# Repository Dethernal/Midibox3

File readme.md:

# MidiBox3

My attempt to make new Waveblaster-compatible interface board.

## Features

* Work with all current loop MIDI source
* Additional Note On volume control with rotary encoder
* Can work without microcontroller as simple interface board but other features will gone.

## Plans

Measure power consumption. What maximum current on +5V line is? Do I really need output filter and what parameters it must have? So, I need to characterize all imortant parameters.

Next, there are more components on PCB that really needed for working. Also some components are more expensive than necessary. It will be reasonable to find cheaper ones.

Finally, STM32F103CBT6 is a beast and I love it. It have USB support and I planned use it in next revision of PCB. I don't know about ADC out via USB, but as power source and MIDI in port it will definitely work. Maybe it also may work as HardMPU, but this will require special DOS driver and I think it has lower priority.

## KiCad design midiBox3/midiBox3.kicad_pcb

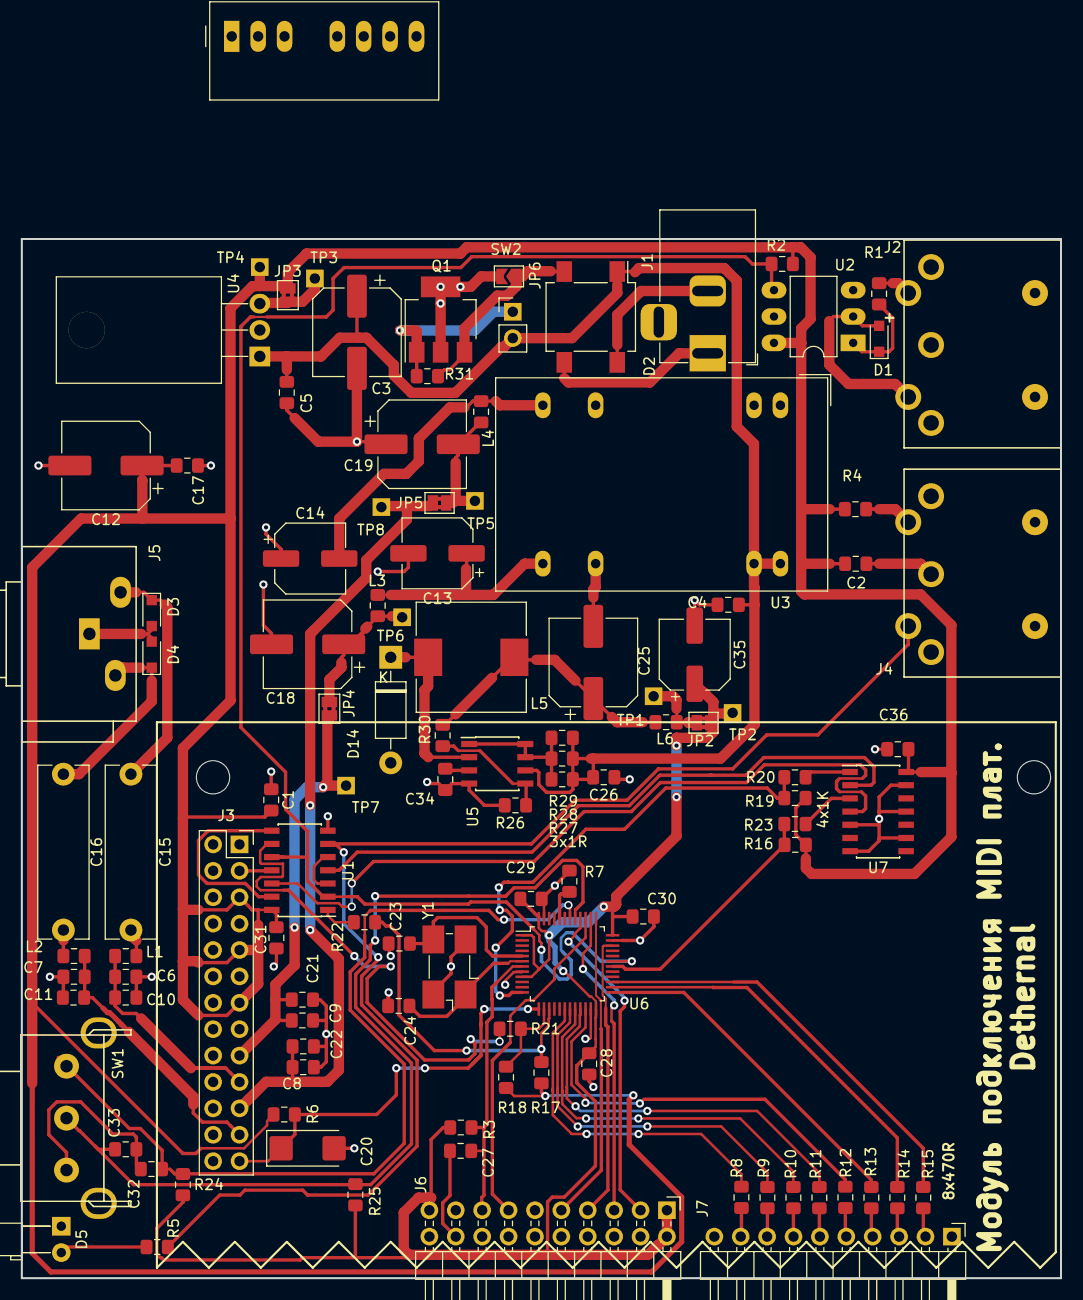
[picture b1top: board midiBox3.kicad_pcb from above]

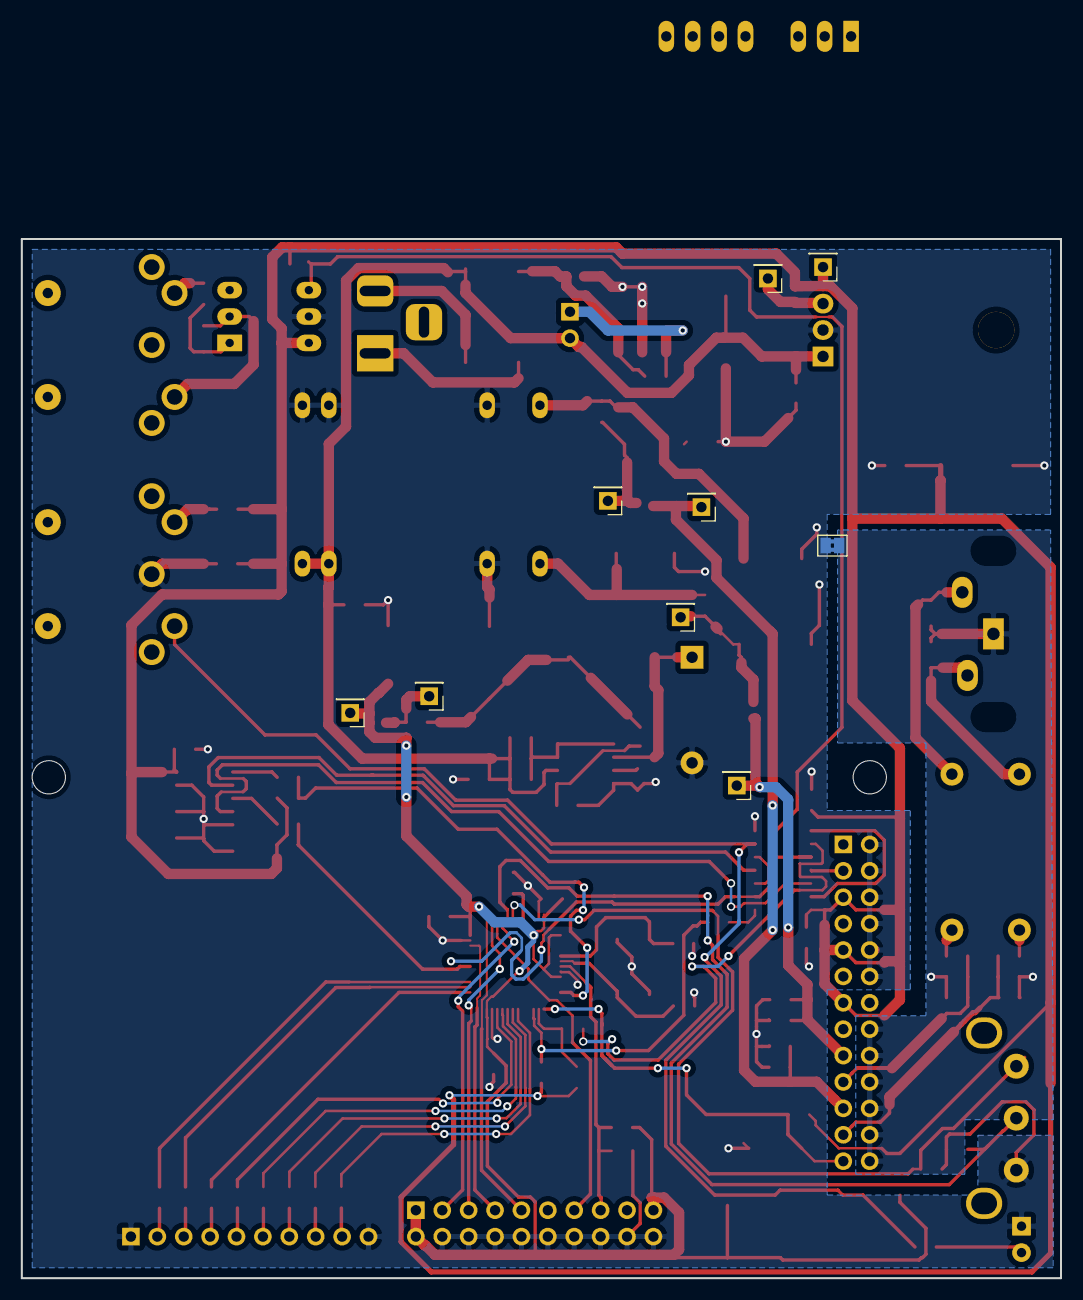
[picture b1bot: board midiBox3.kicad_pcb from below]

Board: 2 copper layers, 100.0 x 100.0 mm, 111 parts (9 on the bottom side), 76 nets.

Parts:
C1, C2, C8, C9, C27, C28, C31, C36: 100pF; C_0805_2012Metric_Pad1.15x1.40mm_HandSolder
C3, C12, C18, C19, C25: 220uF; CP_Elec_8x6.9
C4, C5, C17, C21, C22, C26: 1uF; C_0805_2012Metric_Pad1.15x1.40mm_HandSolder
C6, C7: 47pF; C_0805_2012Metric_Pad1.15x1.40mm_HandSolder
C10, C11, C23, C24: 15pF; C_0805_2012Metric_Pad1.15x1.40mm_HandSolder
C13, C14, C35: 47uF; CP_Elec_6.3x5.9
C15, C16: 1uF; C_Rect_L16.5mm_W4.7mm_P15.00mm_MKT
C20: 10uF; CP_EIA-6032-15_Kemet-U_Pad2.25x2.35mm_HandSolder
C29, C32, C33: 100nF; C_0805_2012Metric_Pad1.15x1.40mm_HandSolder
C30: 10nF; C_0805_2012Metric_Pad1.15x1.40mm_HandSolder
C34: 470pF; C_0805_2012Metric_Pad1.15x1.40mm_HandSolder
D1: 1N4148; D_SOD-323_HandSoldering
D2: DB104; Diode_Bridge_Vishay_DFSFlat
D3, D4: PESD5V0S1BA; D_SOD-323_HandSoldering
D5: LED; LED_D3.0mm_Horizontal_O3.81mm_Z2.0mm
D14: 1N5819; D_DO-41_SOD81_P10.16mm_Horizontal
J1: BarrelJack; BarrelJack_Horizontal
J2: DIN5 IN; DS-5-01
J3: WaveBlaster; PinSocket_2x13_P2.54mm_Vertical
J4: DIN5 OUT; DS-5-01
J5: RSA 2x; RCA_Dual_Jack_Board_RS-209_03x3mm_Vertical
J6: STM32_PROG; PinHeader_2x10_P2.54mm_Horizontal
J7: LED_CON; PinHeader_1x10_P2.54mm_Horizontal
JP1, JP2, JP3, JP4, JP5: SolderJumper-2_P1.3mm_Bridged2Bar_Pad1.0x1.5mm
JP6: shunt; SolderJumper-2_P1.3mm_Open_TrianglePad1.0x1.5mm
L1, L2: 100nH; L_0805_2012Metric_Pad1.15x1.40mm_HandSolder
L3, L4: 33nH; L_0805_2012Metric_Pad1.15x1.40mm_HandSolder
L5: 220 uH; L_10.4x10.4_H4.8
L6: 100 nH; L_0805_2012Metric_Pad1.15x1.40mm_HandSolder
Q1: IRFL110; SOT-223
R1: 510R; R_0805_2012Metric_Pad1.15x1.40mm_HandSolder
R2: 270R; R_0805_2012Metric_Pad1.15x1.40mm_HandSolder
R3, R6, R24, R25: 10K; R_0805_2012Metric_Pad1.15x1.40mm_HandSolder
R4: 220R; R_0805_2012Metric_Pad1.15x1.40mm_HandSolder
R5, R8, R9, R10, R11, R12, R13, R14, R15: 470R; R_0805_2012Metric_Pad1.15x1.40mm_HandSolder
R7: 4.7K; R_0805_2012Metric_Pad1.15x1.40mm_HandSolder
R16, R17, R18, R19, R20, R21, R22, R23: 1K; R_0805_2012Metric_Pad1.15x1.40mm_HandSolder
R26: 1.5K; R_0805_2012Metric_Pad1.15x1.40mm_HandSolder
R27, R28, R29: 1R; R_0805_2012Metric_Pad1.15x1.40mm_HandSolder
R30: 2.7K; R_0805_2012Metric_Pad1.15x1.40mm_HandSolder
R31: 22K; R_0805_2012Metric_Pad1.15x1.40mm_HandSolder
SW1: D_VALUE; Rotary_Encoder_Bourns_PEC16-2215F-N0024_Horizontal_16mm
SW2: SW_Reed; PinHeader_1x02_P2.54mm_Vertical
TP1, TP2, TP3, TP4, TP5, TP6, TP7, TP8: PinHeader_1x01_P2.54mm_Vertical
U1: 74HCT00; SOIC-14_3.9x8.7mm_P1.27mm
U2: H11L1; DIP-6_W7.62mm_LongPads
U3: JTE0624D12; Converter_DCDC_XP_POWER_JTExxxxDxx_THT
U4: L7805; TO-220-3_Horizontal_TabDown
U5: MC33063AD; SOIC-8_3.9x4.9mm_P1.27mm
U6: STM32F103CBT6; LQFP-48_7x7mm_P0.5mm
U7: 74ACT04; SOIC-14_3.9x8.7mm_P1.27mm
Y1: 16MHz; Crystal_SMD_0603-4Pin_6.0x3.5mm_HandSoldering

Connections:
+3V3: C28.2, C29.2, C30.2, C35.1, J6.1, J6.2, J6.19, JP2.2, R3.2, R24.2, R25.2, TP2.1, U6.1, U6.9, U6.24, U6.36, U6.48
+5V: C1.2, C2.2, C12.1, C17.1, C31.2, C36.2, J3.5, J3.9, J3.13, JP3.2, R2.2, R4.2, R6.1, R16.2, R17.2, R18.2, R19.2, TP4.1, U1.14, U2.6, U7.14
+12V: C9.1, C21.1, J3.17, JP4.2, TP7.1
-12V: C8.1, C22.2, J3.21, JP5.2, TP8.1
/+12NF: C13.1, L3.1, U3.14
/+IN12V: C3.1, C4.1, C5.1, C26.1, D2.1, R27.2, R28.2, R29.2, SW2.2, U3.22, U3.23, U4.1, U5.6
/-12NF: C14.2, L4.1, U3.11
/ENC_A: C33.2, R25.1, SW1.B, U6.41
/ENC_B: C32.1, R24.1, SW1.A, U6.42
/JNTRST: J6.3, U6.40
/JTCK_SWCLK: J6.9, U6.37
/JTDI: J6.5, U6.38
/JTDO-TRACESWO: J6.13, U6.39
/JTMS-SWDIO: J6.7, U6.34
/LEFT: C7.1, C11.1, J3.23, L2.1
/MIDI_IN: R2.1, U1.2, U1.10, U2.4, U6.31
/MIDI_N: D1.2, J2.4, U2.2
/MIDI_OUT_CON: R22.2, U1.1
/MIDI_P: D1.1, R1.1, U2.1
/MIDI_WB: J3.3, U1.11
/MIDI_WB_CON: R21.2, U1.9
/NRST: C27.2, J6.15, R3.1, U6.7
/RIGHT: C6.1, C10.1, J3.19, L1.1
/TX1: R23.2, U7.3
/TX2: R20.2, U7.1
/~RESET: C20.1, J3.25, R6.2, U6.13
GNDA: C6.2, C7.2, C10.2, C11.2, D3.2, D4.2, J3.16, J3.18, J3.20, J3.22, J3.24, J3.26, J5.3, JP1.2
GNDD: C1.1, C2.1, C3.2, C4.2, C5.2, C8.2, C9.2, C12.2, C13.2, C14.1, C17.2, C18.2, C19.1, C20.2, C21.2, C22.1, C23.2, C24.2, C25.2, C26.2, C27.1, C28.1, C29.1, C30.1, C31.1, C32.2, C33.1, C34.2, C35.2, C36.1, D5.1, D14.2, J3.2, J3.4, J3.6, J3.8, J3.10, J3.12, J4.2, J6.4, J6.6, J6.8, J6.10, J6.12, J6.14, J6.16, J6.18, J6.20, J7.1, J7.10, JP1.1, JP6.2, Q1.2, Q1.4, R7.2, R26.1, SW1.C, U1.7, U2.5, U3.2, U3.3, U3.9, U3.16, U4.2, U5.4, U6.8, U6.23, U6.35, U6.47, U7.5, U7.7, U7.9, U7.11, U7.13, Y1.2, Y1.4
unnamed: C15.1, D3.1, J5.1
unnamed: C15.2, L1.2
unnamed: C16.1, D4.1, J5.2
unnamed: C16.2, L2.2
unnamed: C18.1, JP4.1, L3.2, TP6.1
unnamed: C19.2, JP5.1, L4.2, TP5.1
unnamed: C23.1, U6.5, Y1.3
unnamed: C24.1, U6.6, Y1.1
unnamed: C25.1, L5.2, L6.1, R30.2
unnamed: C34.1, U5.3
unnamed: D2.2, JP6.1, Q1.3, R31.1
unnamed: D2.3, J1.1
unnamed: D2.4, J1.2
unnamed: D5.2, R5.1
unnamed: D14.1, L5.1, U5.2
unnamed: J2.5, R1.2
unnamed: J4.4, R5.2, U1.6
unnamed: J4.5, R4.1
unnamed: J7.2, R15.2
unnamed: J7.3, R14.2
unnamed: J7.4, R13.2
unnamed: J7.5, R12.2
unnamed: J7.6, R11.2
unnamed: J7.7, R10.2
unnamed: J7.8, R9.2
unnamed: J7.9, R8.2
unnamed: JP2.1, L6.2, TP1.1
unnamed: JP3.1, TP3.1, U4.3
unnamed: Q1.1, R31.2, SW2.1
unnamed: R7.1, U6.44
unnamed: R8.1, U6.18
unnamed: R9.1, U6.19
unnamed: R10.1, U6.20
unnamed: R11.1, U6.21
unnamed: R12.1, U6.22
unnamed: R13.1, U6.25
unnamed: R14.1, U6.26
unnamed: R15.1, U6.27
unnamed: R16.1, R23.1, U6.30
unnamed: R17.1, R22.1, U6.15
unnamed: R18.1, R21.1, U6.14
unnamed: R19.1, R20.1, U6.12
unnamed: R26.2, R30.1, U5.5
unnamed: R27.1, R28.1, R29.1, U5.1, U5.7, U5.8
unnamed: U1.3, U1.5
unnamed: U1.4, U7.2
unnamed: U1.12, U7.4
unnamed: U1.8, U1.13

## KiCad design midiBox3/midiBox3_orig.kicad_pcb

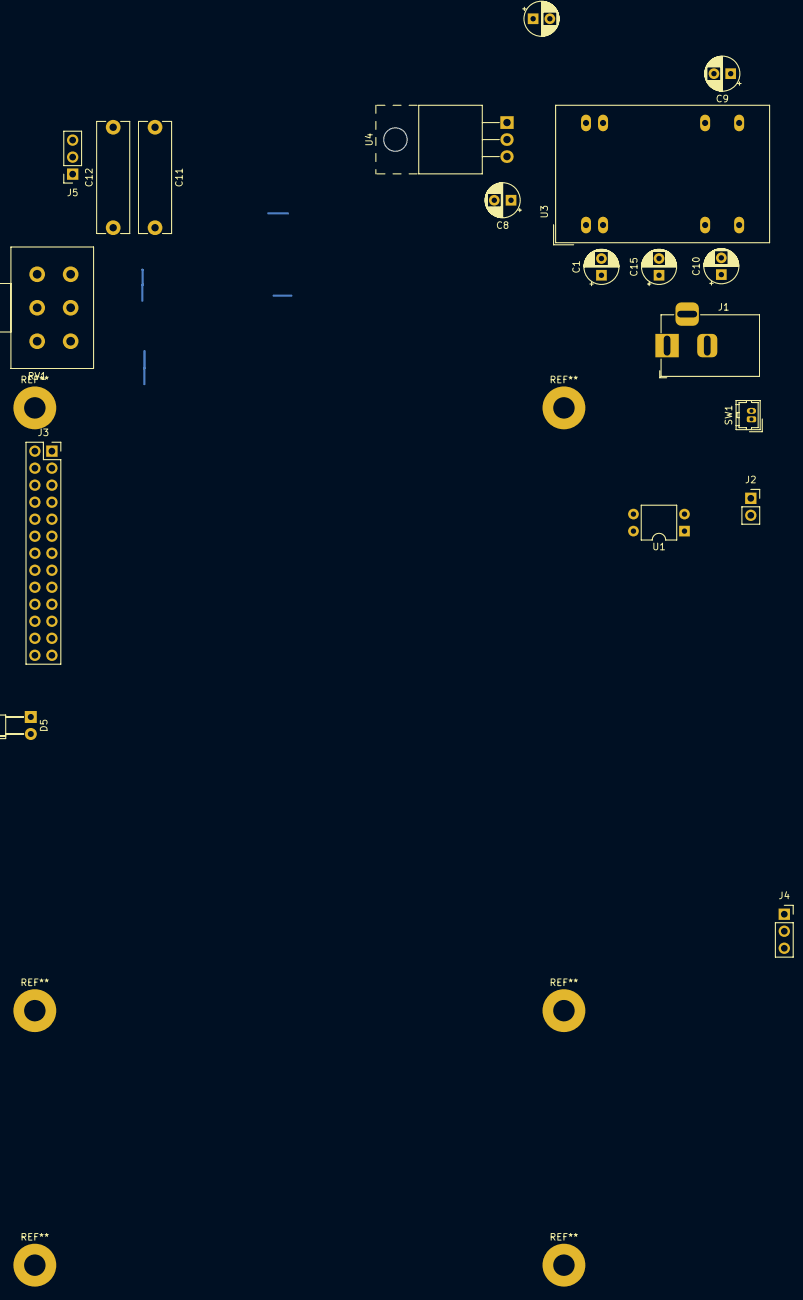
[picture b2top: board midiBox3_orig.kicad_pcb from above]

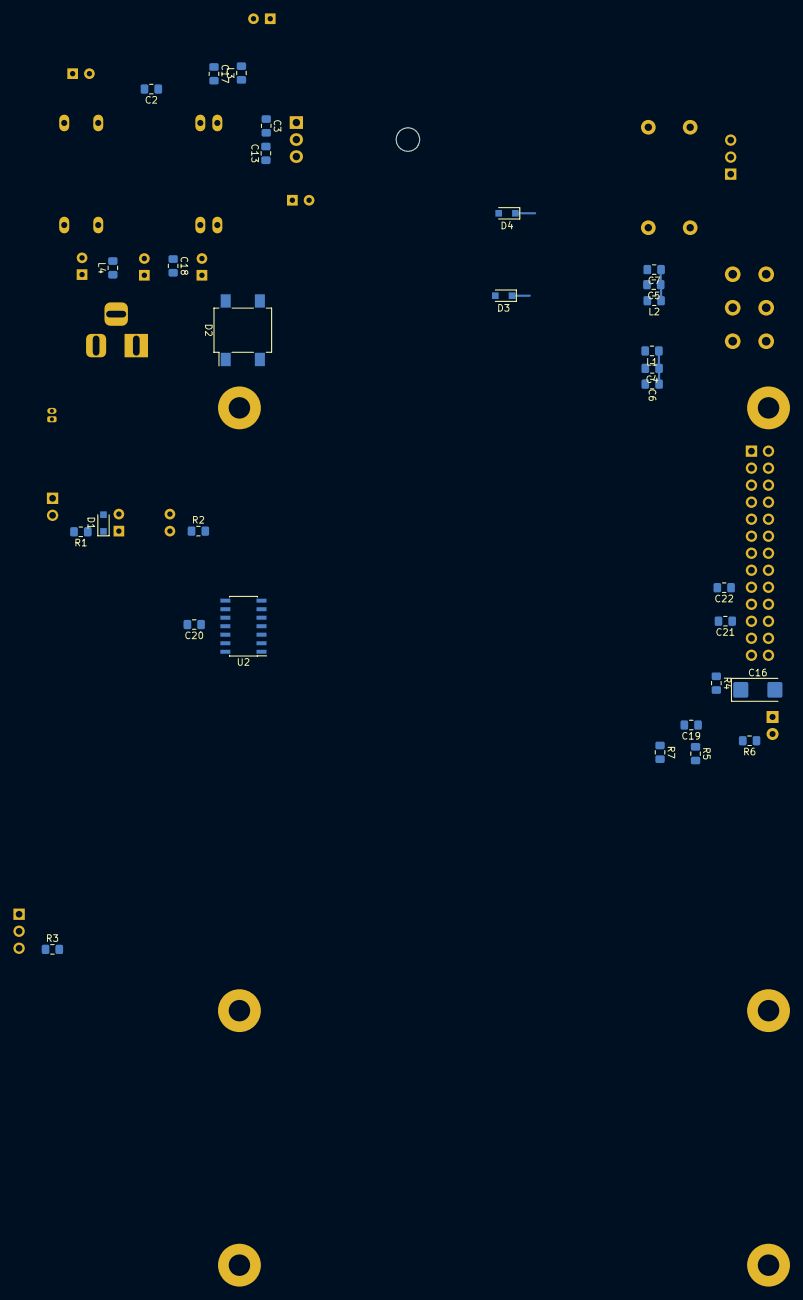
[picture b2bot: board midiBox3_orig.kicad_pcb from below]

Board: 2 copper layers, 49 parts (30 on the bottom side), 29 nets.

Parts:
C1, C8, C14, C15: 220uF; CP_Radial_D5.0mm_P2.50mm
C2, C3, C13, C17, C18: 1uF; C_0805_2012Metric_Pad1.15x1.40mm_HandSolder
C4, C5: 47pF; C_0805_2012Metric_Pad1.15x1.40mm_HandSolder
C6, C7: 15pF; C_0805_2012Metric_Pad1.15x1.40mm_HandSolder
C9, C10: 47uF; CP_Radial_D5.0mm_P2.50mm
C11, C12: 1uF; C_Rect_L16.5mm_W4.7mm_P15.00mm_MKT
C16: 10uF; CP_EIA-6032-15_Kemet-U_Pad2.25x2.35mm_HandSolder
C19, C20, C21, C22: 100pF; C_0805_2012Metric_Pad1.15x1.40mm_HandSolder
D1: 1N4148; D_SOD-323_HandSoldering
D2: DB104; Diode_Bridge_Vishay_DFSFlat
D3, D4: PESD5V0S1BA; D_SOD-323_HandSoldering
D5: LED; LED_D3.0mm_Horizontal_O3.81mm_Z2.0mm
J1: Barrel_Jack_Switch; BarrelJack_Horizontal
J2: H2; PinSocket_1x02_P2.54mm_Vertical
J3: Conn_02x13_Odd_Even; PinSocket_2x13_P2.54mm_Vertical
J4: H3; PinSocket_1x03_P2.54mm_Vertical
J5: Conn_Coaxial_x2; PinSocket_1x03_P2.54mm_Vertical
L1, L2: 100nH; L_0805_2012Metric_Pad1.15x1.40mm_HandSolder
L3, L4: 33nH; L_0805_2012Metric_Pad1.15x1.40mm_HandSolder
R1, R3: 220R; R_0805_2012Metric_Pad1.15x1.40mm_HandSolder
R2: 4.7K; R_0805_2012Metric_Pad1.15x1.40mm_HandSolder
R4: 10K; R_0805_2012Metric_Pad1.15x1.40mm_HandSolder
R5, R7: 0R; R_0805_2012Metric_Pad1.15x1.40mm_HandSolder
R6: 470R; R_0805_2012Metric_Pad1.15x1.40mm_HandSolder
RV1: R_POT_Dual; Potentiometer_Alps_RK163_Dual_Horizontal
SW1: SW_DIP_x01; Hirose_DF13-02P-1.25DSA_1x02_P1.25mm_Vertical
U1: PC817; DIP-4_W7.62mm
U2: MM74HCT00M; SOIC-14_3.9x8.7mm_P1.27mm
U3: JTE0624D12; Converter_DCDC_XP_POWER_JTExxxxDxx_THT
U4: LM7805_TO220; TO-220-3_Horizontal_TabUp

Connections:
+5V: C8.1, C13.1, C19.1, C20.1, J3.3, J3.5, J3.9, J3.13, R2.2, R3.2, R4.1, U2.11, U2.14, U4.3
+12V: C14.1, C17.1, C22.1, J3.17, L3.2
-12V: C15.1, C18.2, C21.1, J3.21, L4.2
/LEFT: J3.23, RV1.2
/RIGHT: J3.19, RV1.5
/~RESET: C16.1, J3.25, R4.2
GND: C1.2, C2.2, C3.2, C4.2, C5.2, C6.2, C7.2, C8.2, C9.2, C10.2, C13.2, C14.2, C15.2, C16.2, C17.2, C18.1, C19.2, C20.2, C21.2, C22.2, D2.4, D3.2, D4.2, D5.1, J3.2, J3.4, J3.6, J3.8, J3.10, J3.12, J3.16, J3.18, J3.20, J3.22, J3.24, J3.26, J4.2, J5.3, RV1.1, RV1.4, U1.3, U2.7, U3.2, U3.3, U3.9, U3.16, U4.2
unnamed: C1.1, C2.1, C3.1, D2.3, U3.22, U3.23, U4.1
unnamed: C4.1, C6.1, L1.1, RV1.6
unnamed: C5.1, C7.1, L2.1, RV1.3
unnamed: C9.1, L3.1, U3.14
unnamed: C10.1, L4.1, U3.11
unnamed: C11.1, D3.1, J5.1
unnamed: C11.2, L1.2
unnamed: C12.1, D4.1, J5.2
unnamed: C12.2, L2.2
unnamed: D1.1, R1.1, U1.1
unnamed: D1.2, J2.2, U1.2
unnamed: D2.1, SW1.2
unnamed: D2.2, J1.1
unnamed: D5.2, R6.1
unnamed: J1.2, SW1.1
unnamed: J2.1, R1.2
unnamed: J4.1, R7.2, U2.6
unnamed: J4.3, R3.1
unnamed: R2.1, U1.4, U2.1, U2.2, U2.9, U2.10
unnamed: R5.1, R6.2, R7.1
unnamed: R5.2, U2.3, U2.4, U2.5
unnamed: U2.8, U2.12, U2.13

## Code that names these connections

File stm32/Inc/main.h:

/* USER CODE BEGIN Header */
/**
  ******************************************************************************
  * @file           : main.h
  * @brief          : Header for main.c file.
  *                   This file contains the common defines of the application.
  ******************************************************************************
  * @attention
  *
  * <h2><center>&copy; Copyright (c) 2019 STMicroelectronics.
  * All rights reserved.</center></h2>
  *
  * This software component is licensed by ST under BSD 3-Clause license,
  * the "License"; You may not use this file except in compliance with the
  * License. You may obtain a copy of the License at:
  *                        opensource.org/licenses/BSD-3-Clause
  *
  ******************************************************************************
  */
/* USER CODE END Header */

/* Define to prevent recursive inclusion -------------------------------------*/
#ifndef __MAIN_H
#define __MAIN_H

#ifdef __cplusplus
extern "C" {
#endif

/* Includes ------------------------------------------------------------------*/
#include "stm32f1xx_ll_rcc.h"
#include "stm32f1xx_ll_bus.h"
#include "stm32f1xx_ll_system.h"
#include "stm32f1xx_ll_exti.h"
#include "stm32f1xx_ll_cortex.h"
#include "stm32f1xx_ll_utils.h"
#include "stm32f1xx_ll_pwr.h"
#include "stm32f1xx_ll_dma.h"
#include "stm32f1xx_ll_tim.h"
#include "stm32f1xx_ll_usart.h"
#include "stm32f1xx.h"
#include "stm32f1xx_ll_gpio.h"

#if defined(USE_FULL_ASSERT)
#include "stm32_assert.h"
#endif /* USE_FULL_ASSERT */

/* Private includes ----------------------------------------------------------*/
/* USER CODE BEGIN Includes */

/* USER CODE END Includes */

/* Exported types ------------------------------------------------------------*/
/* USER CODE BEGIN ET */

/* USER CODE END ET */

/* Exported constants --------------------------------------------------------*/
/* USER CODE BEGIN EC */

/* USER CODE END EC */

/* Exported macro ------------------------------------------------------------*/
/* USER CODE BEGIN EM */

/* USER CODE END EM */

/* Exported functions prototypes ---------------------------------------------*/
void Error_Handler(void);

/* USER CODE BEGIN EFP */

/* USER CODE END EFP */

/* Private defines -----------------------------------------------------------*/
#define TX2_Pin LL_GPIO_PIN_2
#define TX2_GPIO_Port GPIOA
#define WBRESET_Pin LL_GPIO_PIN_3
#define WBRESET_GPIO_Port GPIOA
#define MIDI_WB_CON_Pin LL_GPIO_PIN_4
#define MIDI_WB_CON_GPIO_Port GPIOA
#define MIDI_OUT_CON_Pin LL_GPIO_PIN_5
#define MIDI_OUT_CON_GPIO_Port GPIOA
#define LED1_Pin LL_GPIO_PIN_0
#define LED1_GPIO_Port GPIOB
#define LED2_Pin LL_GPIO_PIN_1
#define LED2_GPIO_Port GPIOB
#define LED3_Pin LL_GPIO_PIN_2
#define LED3_GPIO_Port GPIOB
#define LED4_Pin LL_GPIO_PIN_10
#define LED4_GPIO_Port GPIOB
#define LED5_Pin LL_GPIO_PIN_11
#define LED5_GPIO_Port GPIOB
#define LED6_Pin LL_GPIO_PIN_12
#define LED6_GPIO_Port GPIOB
#define LED7_Pin LL_GPIO_PIN_13
#define LED7_GPIO_Port GPIOB
#define LED8_Pin LL_GPIO_PIN_14
#define LED8_GPIO_Port GPIOB
#define TX1_Pin LL_GPIO_PIN_9
#define TX1_GPIO_Port GPIOA
#define RX1_Pin LL_GPIO_PIN_10
#define RX1_GPIO_Port GPIOA
#define ENC_A_Pin LL_GPIO_PIN_5
#define ENC_A_GPIO_Port GPIOB
#define ENC_A_EXTI_IRQn EXTI9_5_IRQn
#define ENC_B_Pin LL_GPIO_PIN_6
#define ENC_B_GPIO_Port GPIOB
#define ENC_B_EXTI_IRQn EXTI9_5_IRQn
#ifndef NVIC_PRIORITYGROUP_0
#define NVIC_PRIORITYGROUP_0         ((uint32_t)0x00000007) /*!< 0 bit  for pre-emption priority,
                                                                 4 bits for subpriority */
#define NVIC_PRIORITYGROUP_1         ((uint32_t)0x00000006) /*!< 1 bit  for pre-emption priority,
                                                                 3 bits for subpriority */
#define NVIC_PRIORITYGROUP_2         ((uint32_t)0x00000005) /*!< 2 bits for pre-emption priority,
                                                                 2 bits for subpriority */
#define NVIC_PRIORITYGROUP_3         ((uint32_t)0x00000004) /*!< 3 bits for pre-emption priority,
                                                                 1 bit  for subpriority */
#define NVIC_PRIORITYGROUP_4         ((uint32_t)0x00000003) /*!< 4 bits for pre-emption priority,
                                                                 0 bit  for subpriority */
#endif
/* USER CODE BEGIN Private defines */

#define INTERNAL_USART USART1
#define EXTERNAL_USART USART2

extern uint32_t prev_encoder_pos;

/* USER CODE END Private defines */

#ifdef __cplusplus
}
#endif

#endif /* __MAIN_H */

/************************ (C) COPYRIGHT STMicroelectronics *****END OF FILE****/

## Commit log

2019-04-28 Added readme.md
2019-04-28 Added license file
2019-04-30 First step working on firmware.
2019-04-30 With firmware, Daughterboards are working now
2019-04-30 Changed pcb, fix issue 1
2019-05-01 Added new chip — 7404.
    Because TX signals need to be inverted and MST32 lack of abilities to do so. Updated chematic and pcb.
2019-05-02 Replaced U2 PC817 with H11L1
2020-02-01 Промежуточная версия. Нужно рассчиать какие дополнительные таймеры потребуются для работы.
2020-05-04 Начало реальной работы над HardMPU
2020-05-07 Fiddling here and there.
2020-05-08 Preparing to remove HardMPU code (I cannot get commands via MIDI data chanel to it pointless)
2020-05-08 New version, new hope
2020-05-12 New PCB
